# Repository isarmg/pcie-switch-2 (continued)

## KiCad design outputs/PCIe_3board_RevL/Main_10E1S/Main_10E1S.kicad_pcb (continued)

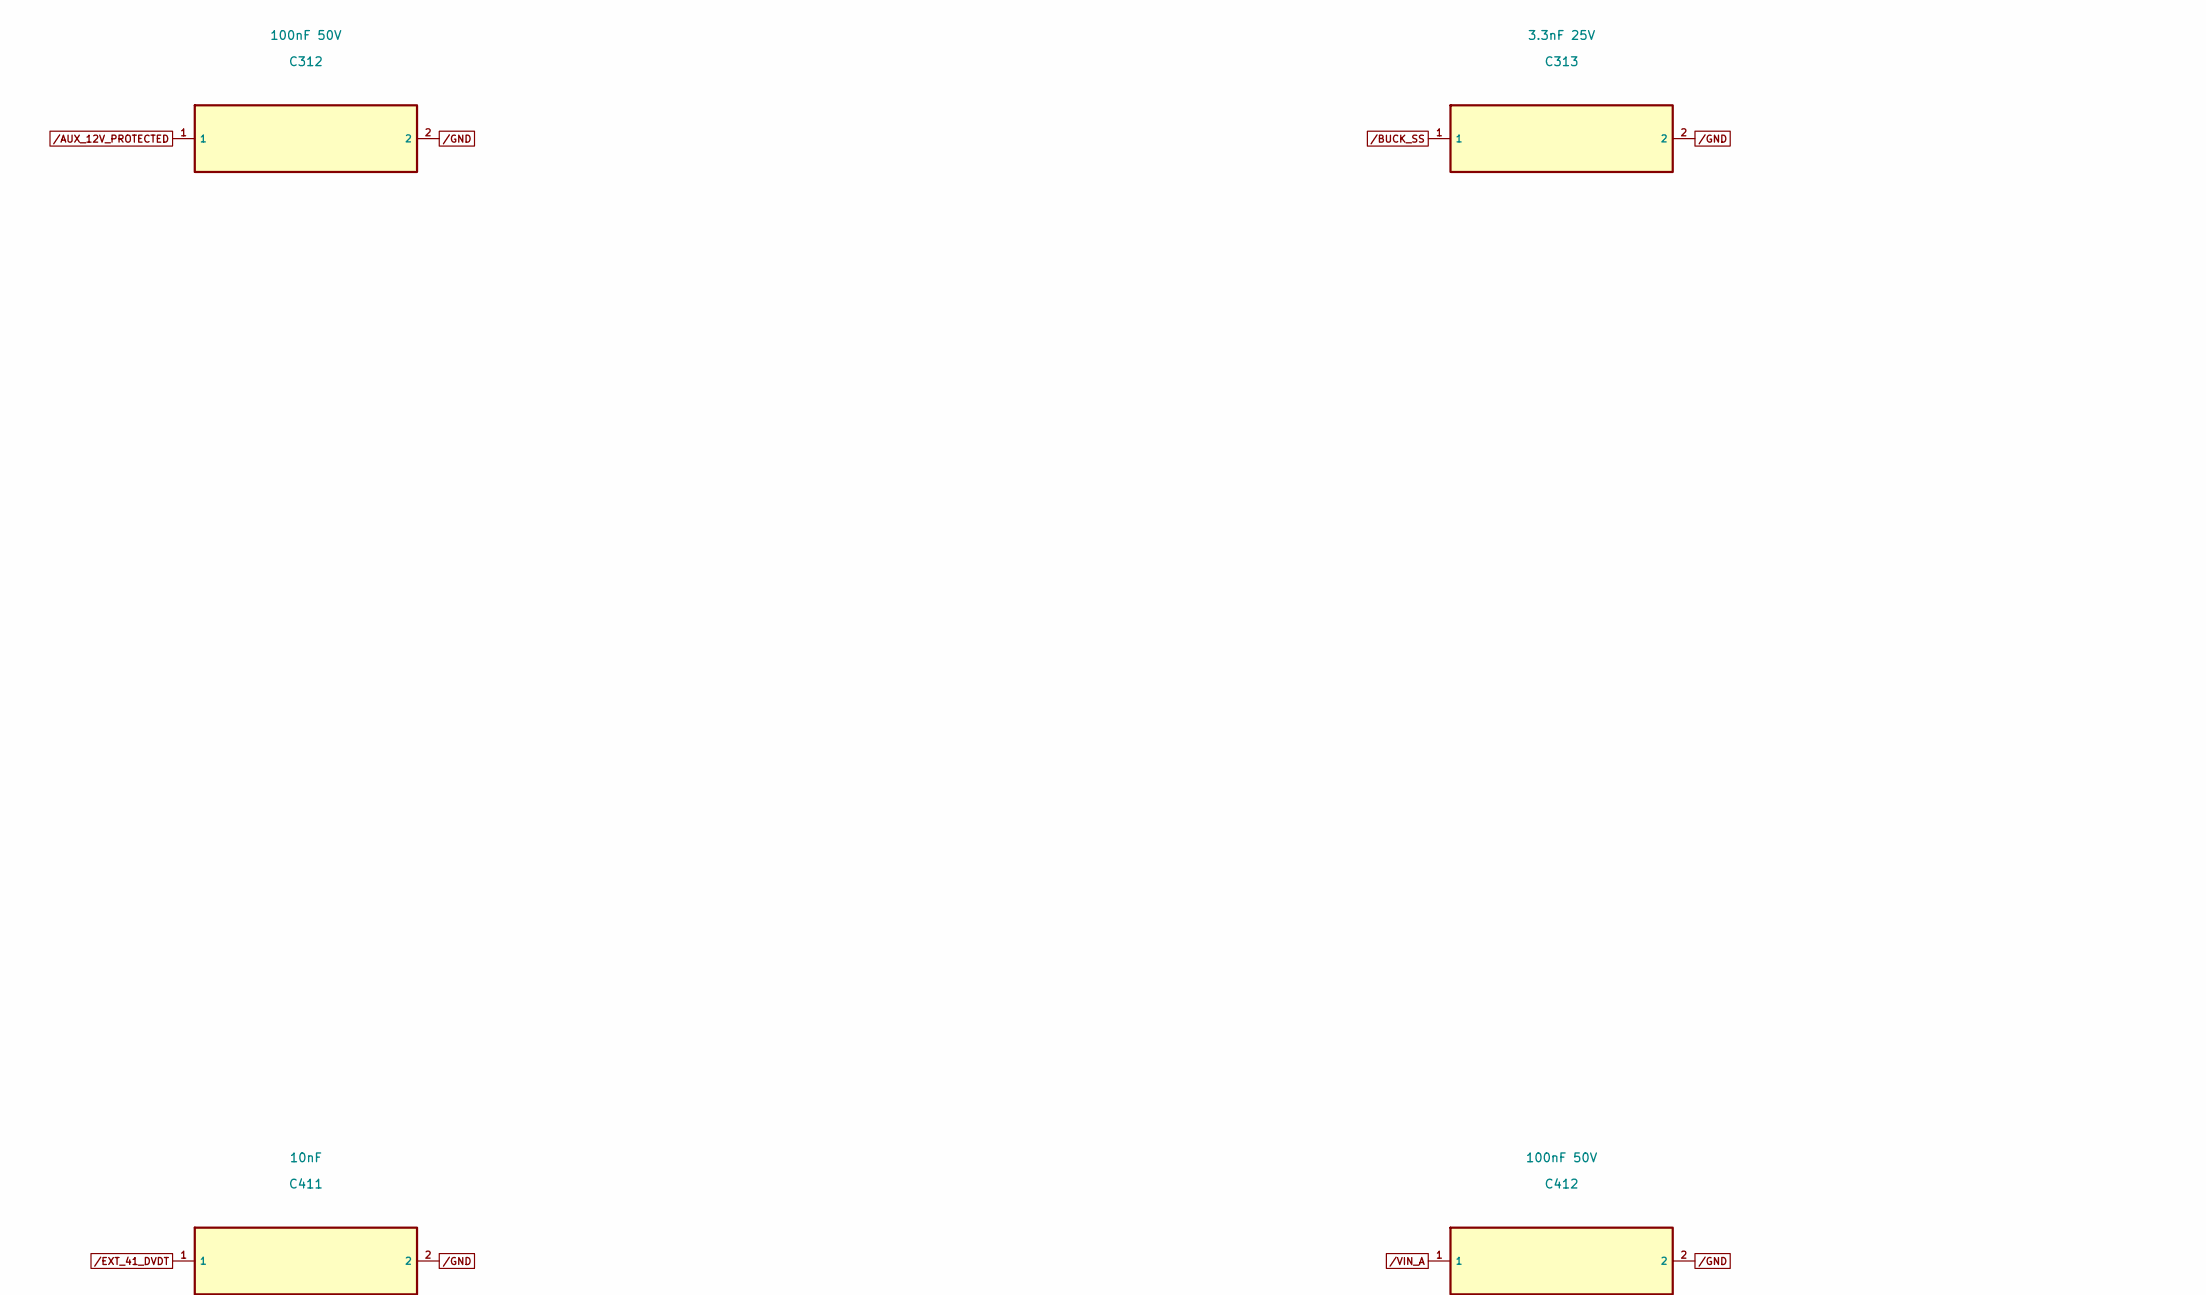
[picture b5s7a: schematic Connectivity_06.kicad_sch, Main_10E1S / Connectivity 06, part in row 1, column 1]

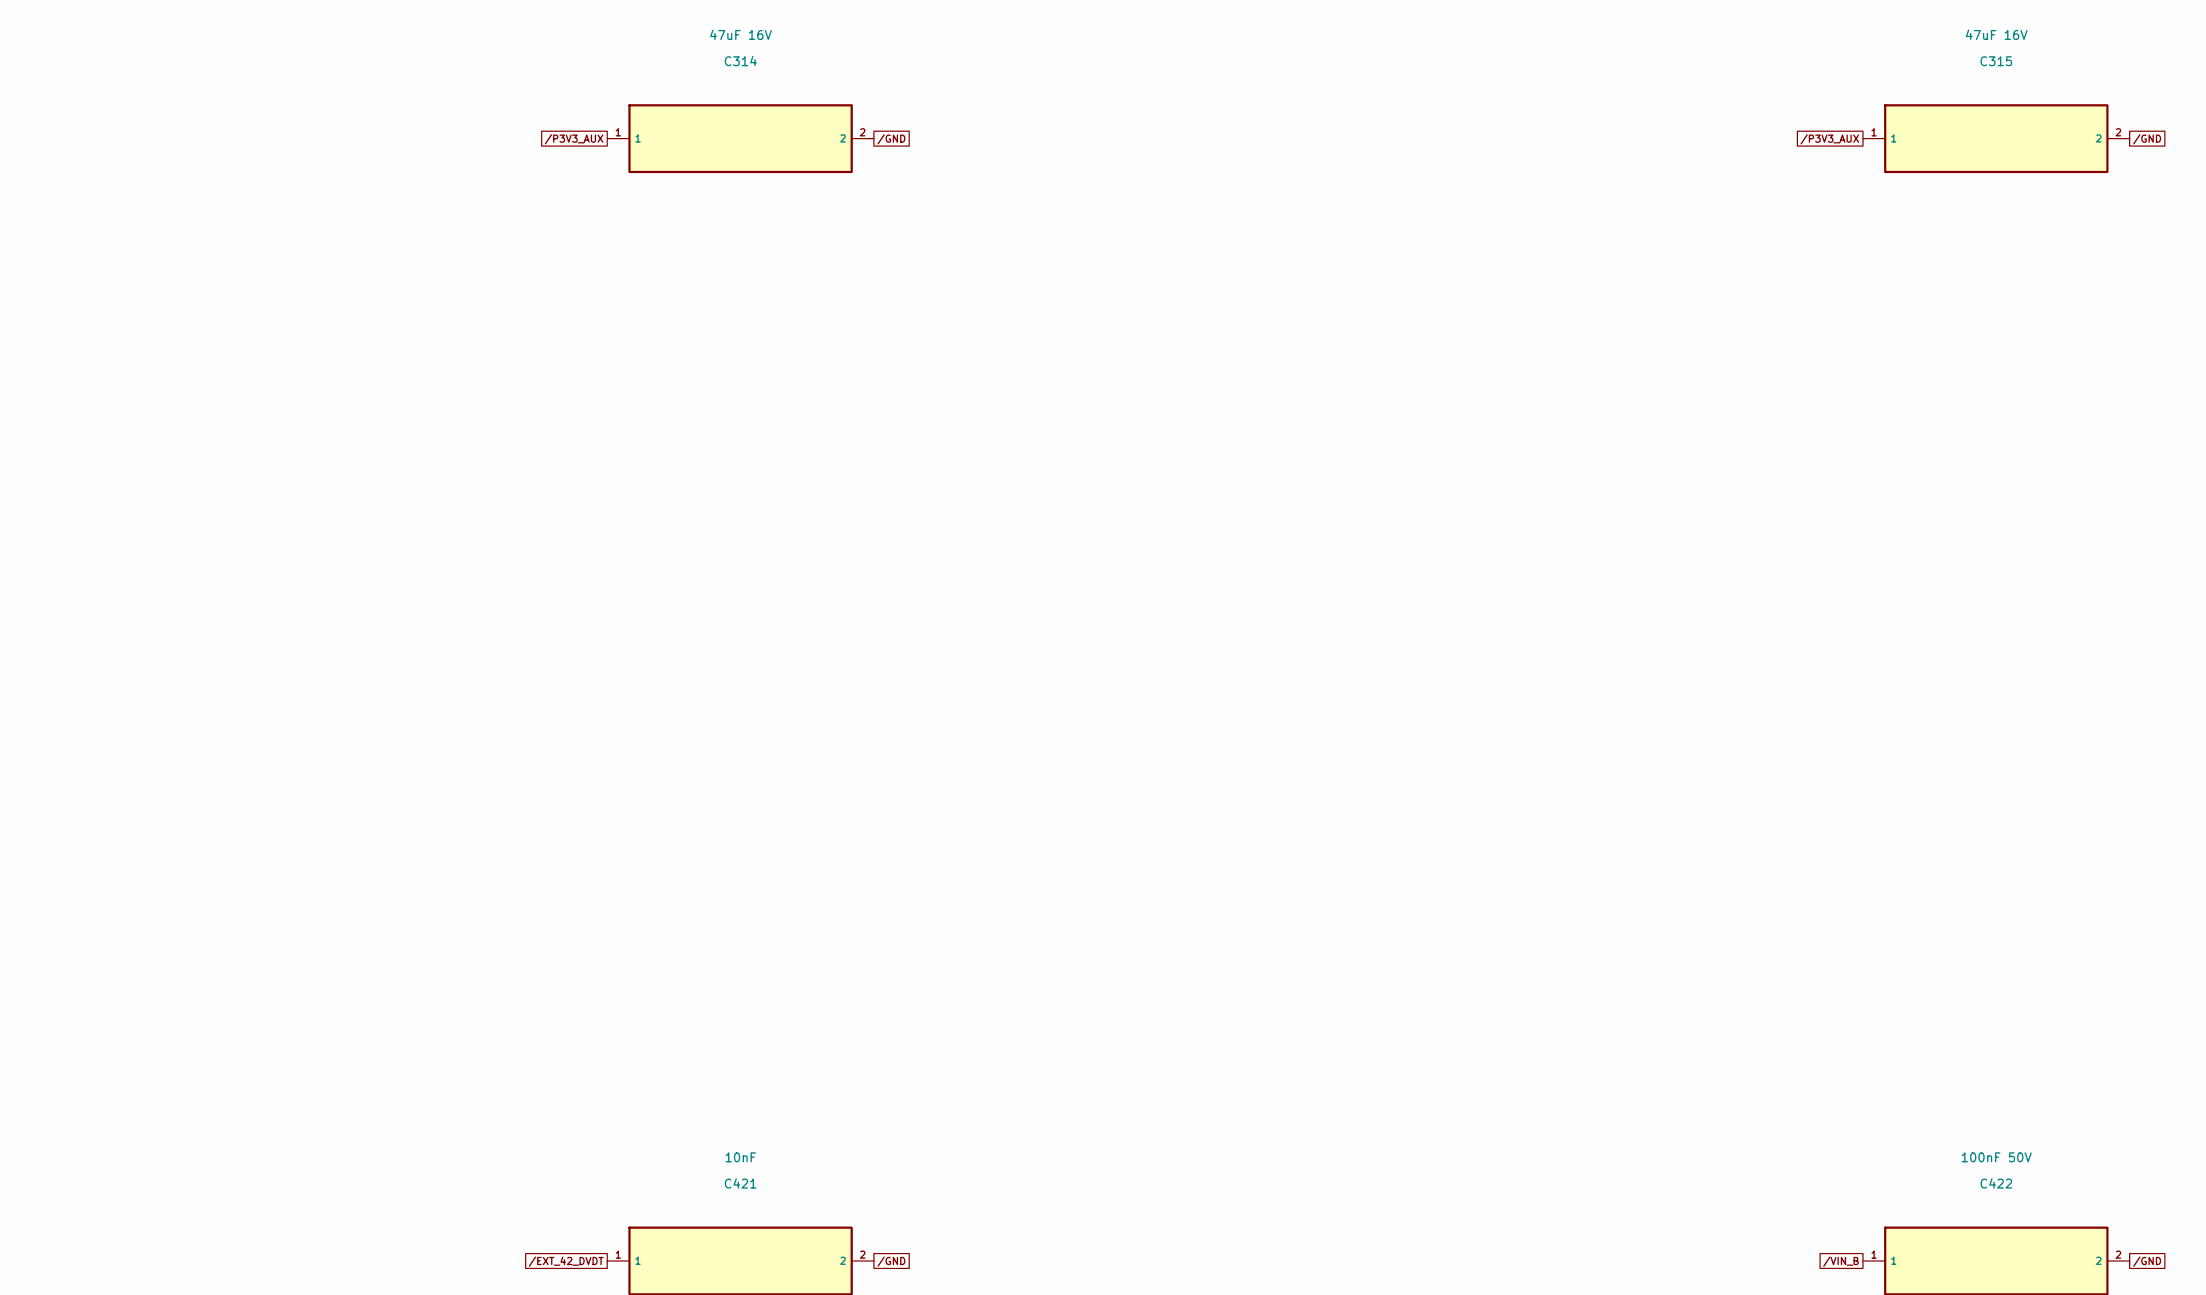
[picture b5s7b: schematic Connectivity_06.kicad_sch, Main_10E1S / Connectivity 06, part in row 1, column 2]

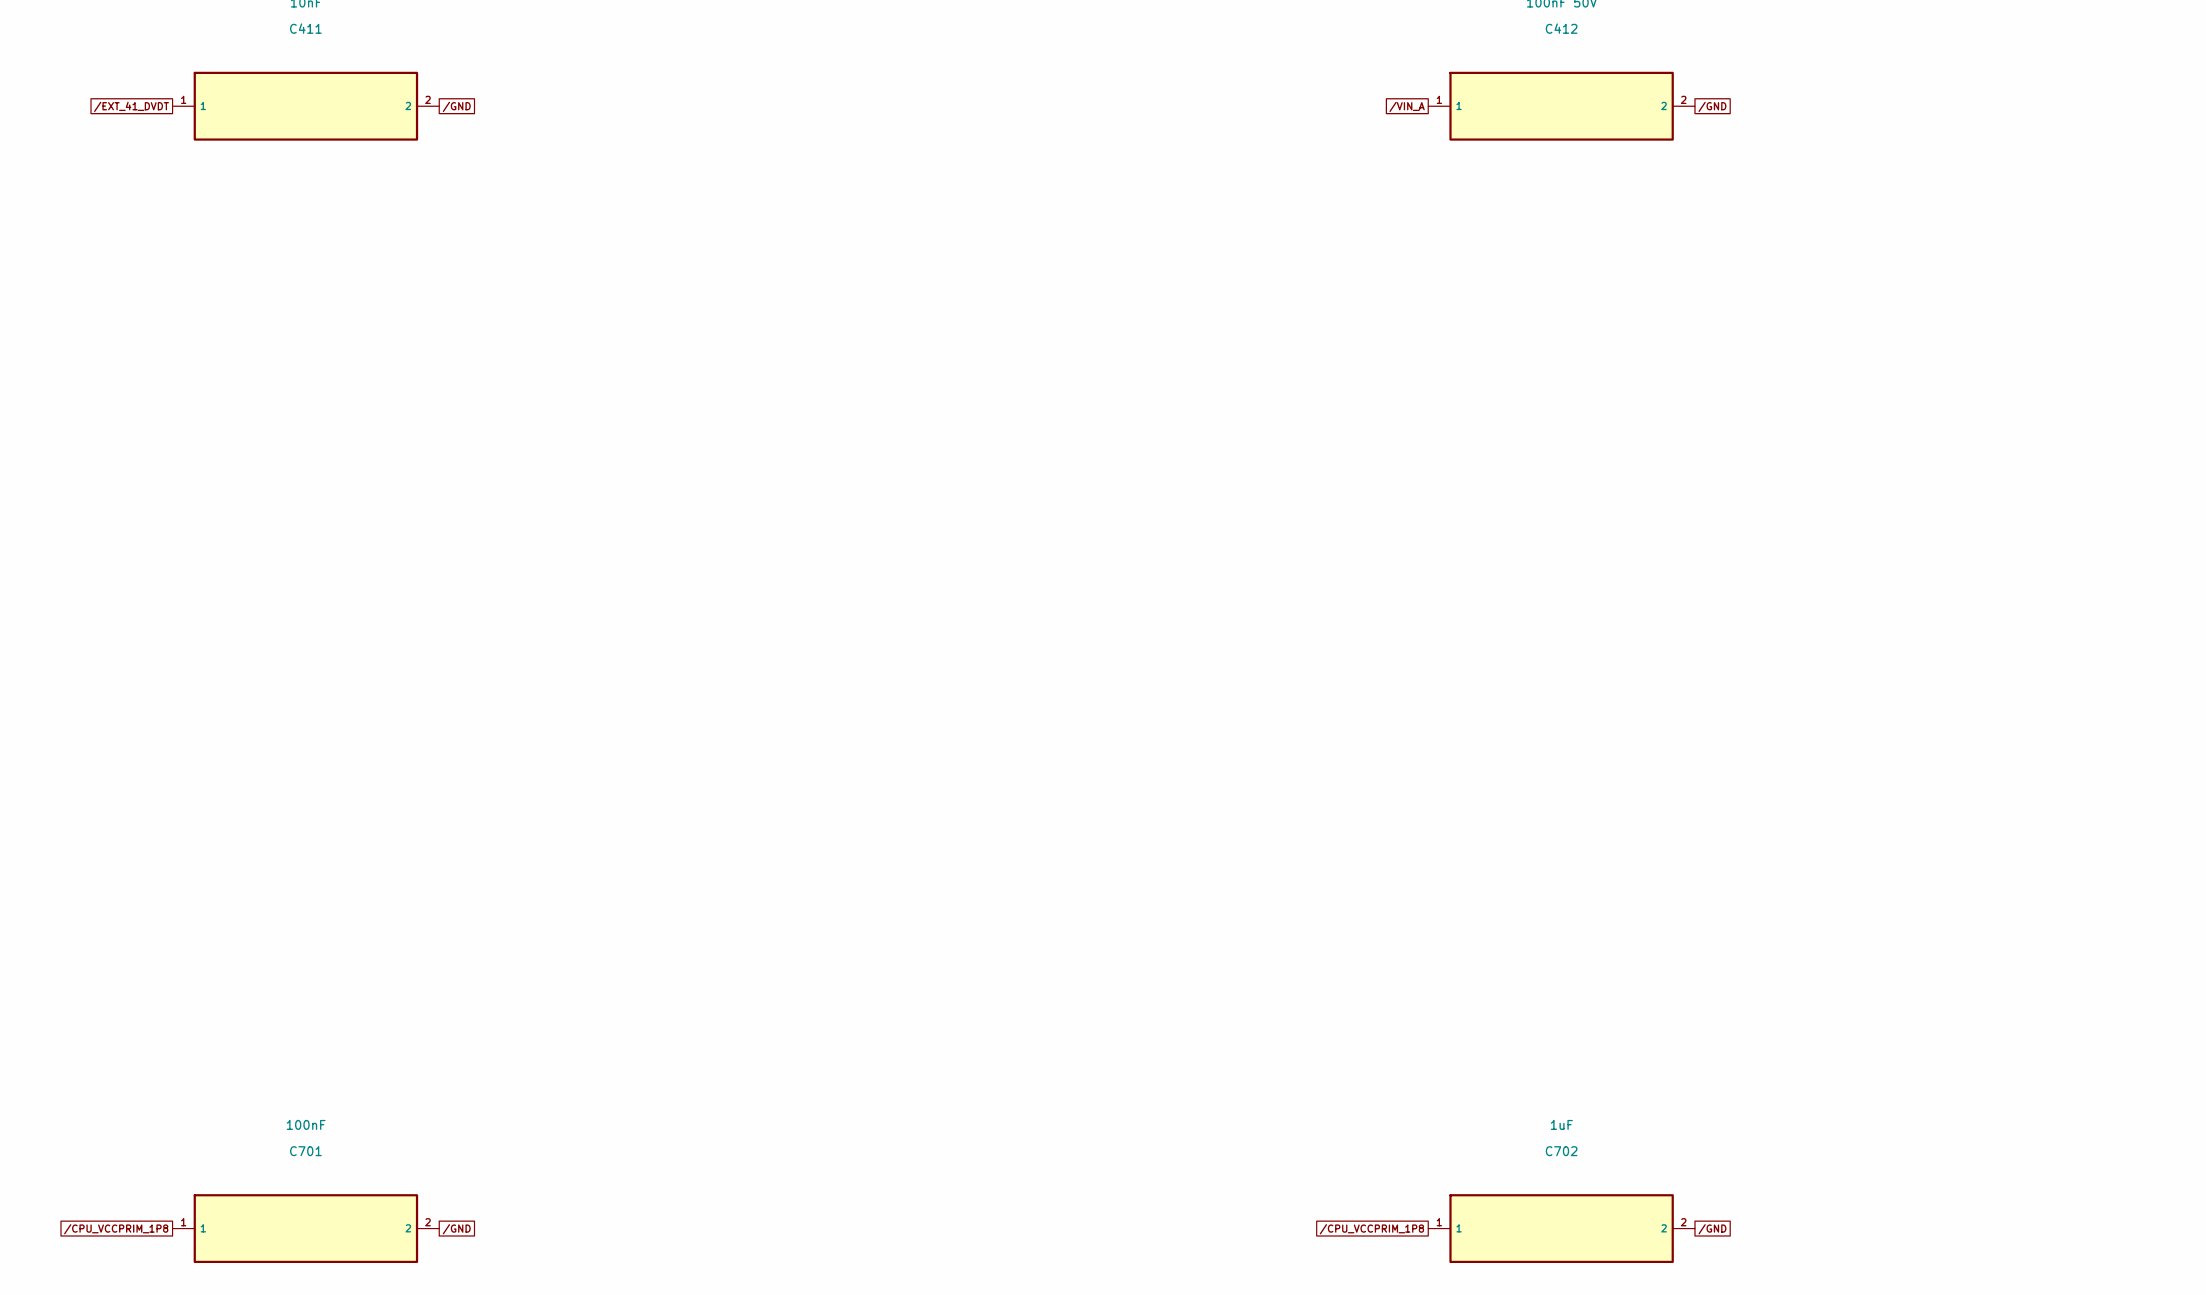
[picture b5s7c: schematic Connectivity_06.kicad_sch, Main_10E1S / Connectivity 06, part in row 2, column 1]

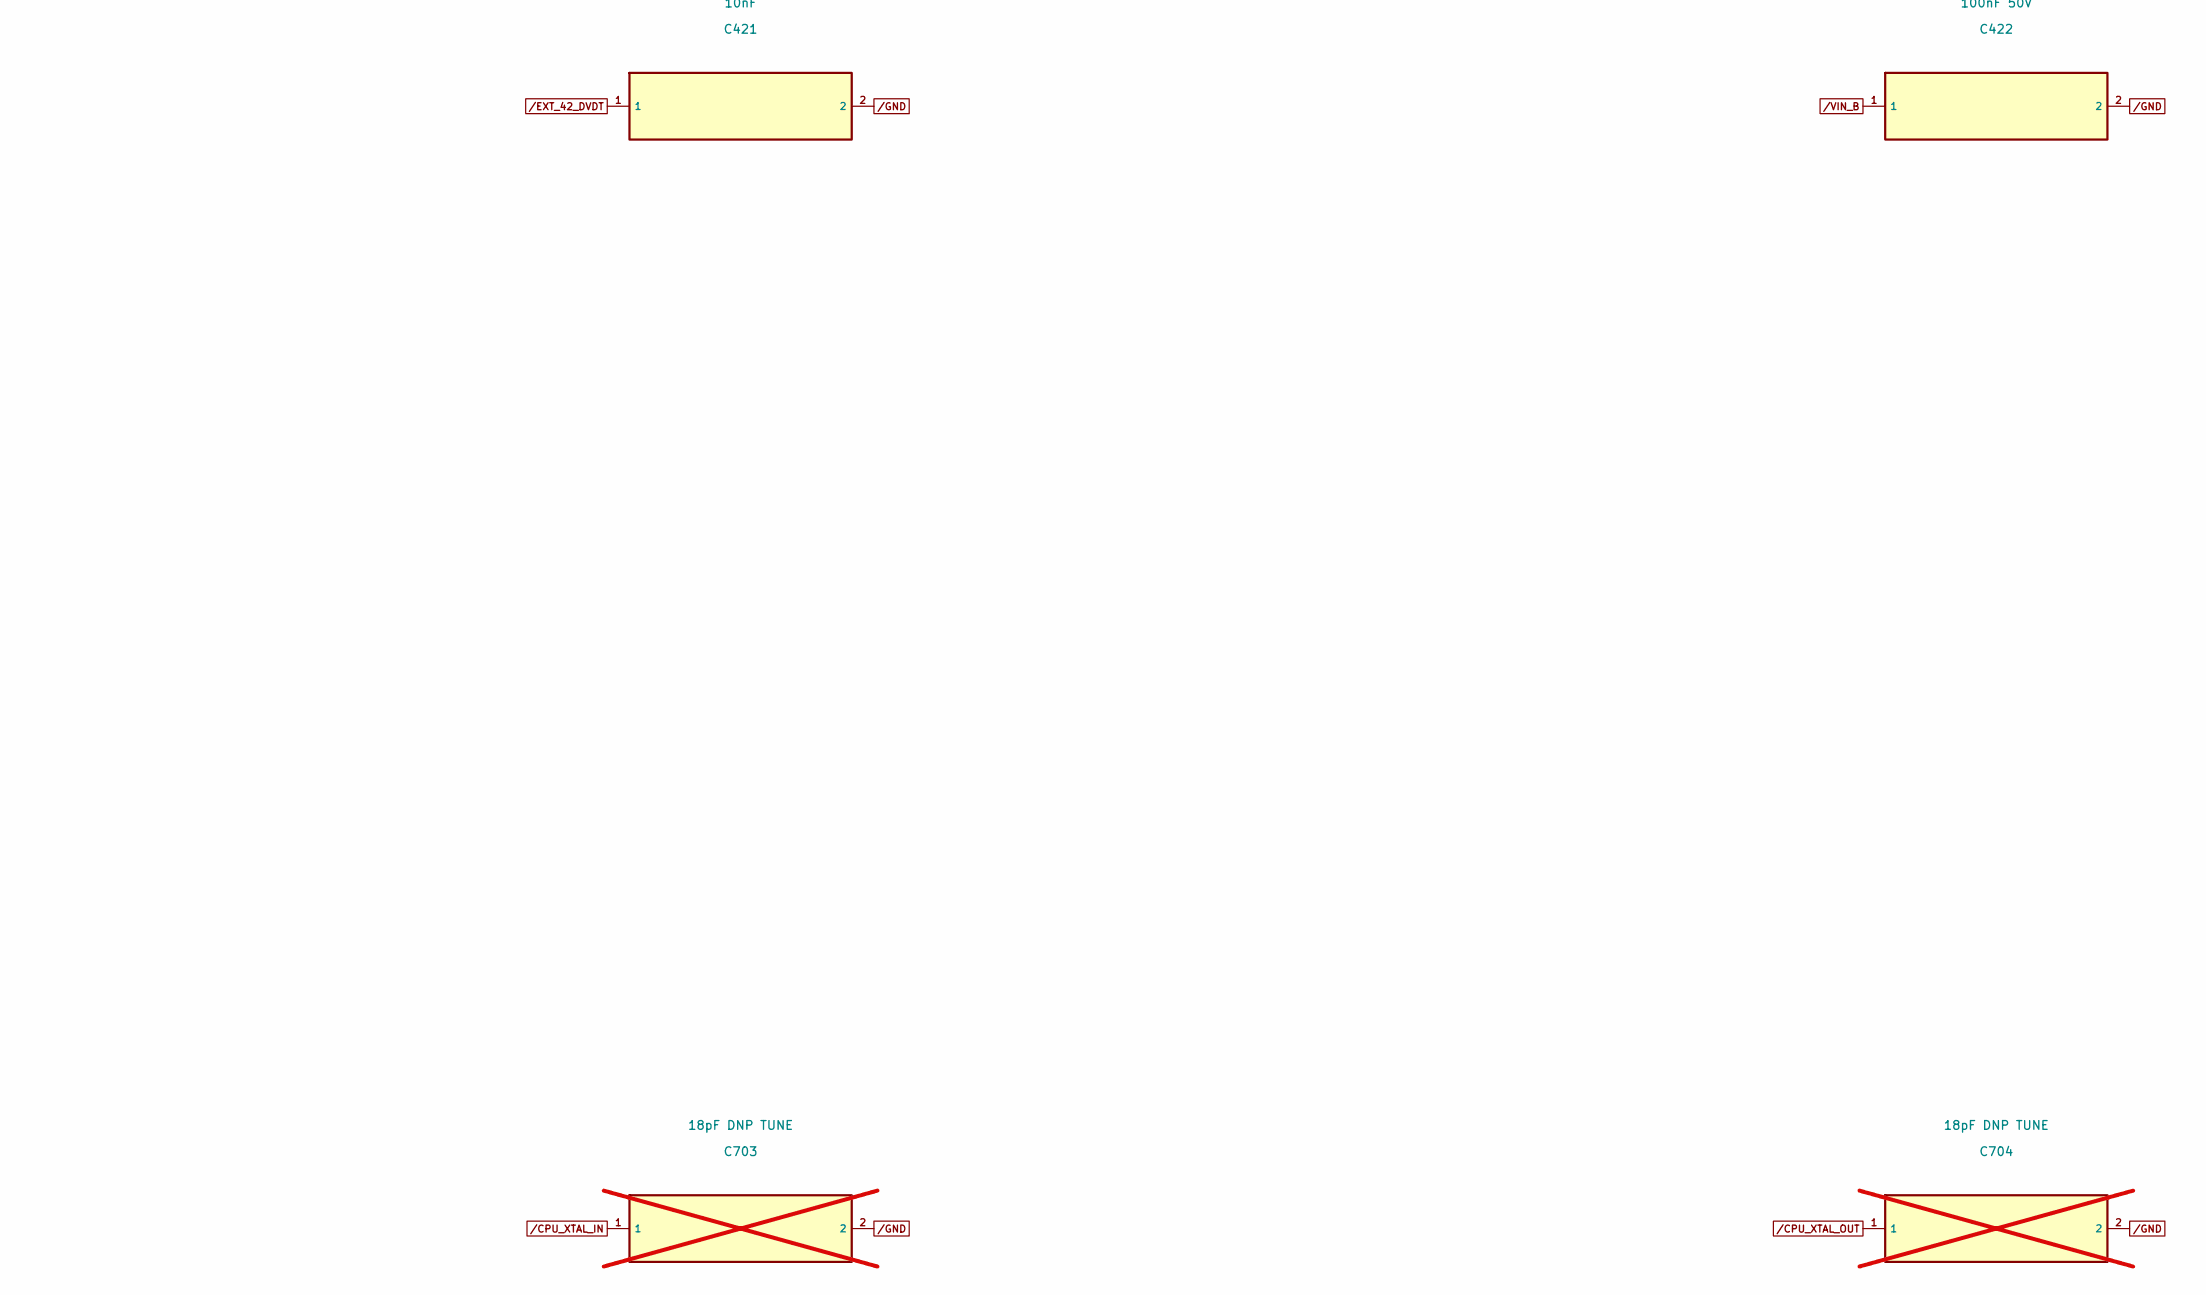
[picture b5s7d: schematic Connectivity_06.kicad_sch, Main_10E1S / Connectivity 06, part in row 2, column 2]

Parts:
C312: 100nF 50V; C_0402_1005Metric
C313: 3.3nF 25V; C_0402_1005Metric
C314, C315: 47uF 16V; C_1210_3225Metric
C411, C421: 10nF; C_0402_1005Metric
C412, C422: 100nF 50V; C_0603_1608Metric
C701: 100nF; C_0402_1005Metric
C702: 1uF; C_0402_1005Metric
C703, C704: 18pF DNP TUNE; C_0402_1005Metric; not fitted

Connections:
/AUX_12V_PROTECTED: C312.1; also elsewhere on the board
/BUCK_SS: C313.1; also elsewhere on the board
/CPU_VCCPRIM_1P8: C701.1, C702.1; also elsewhere on the board
/CPU_XTAL_IN: C703.1; also elsewhere on the board
/CPU_XTAL_OUT: C704.1; also elsewhere on the board
/EXT_41_DVDT: C411.1; also elsewhere on the board
/EXT_42_DVDT: C421.1; also elsewhere on the board
/GND: C312.2, C313.2, C314.2, C315.2, C411.2, C412.2, C421.2, C422.2, C701.2, C702.2, C703.2, C704.2; also elsewhere on the board
/P3V3_AUX: C314.1, C315.1; also elsewhere on the board
/VIN_A: C412.1; also elsewhere on the board
/VIN_B: C422.1; also elsewhere on the board
